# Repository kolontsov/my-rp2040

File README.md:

# My-RP2040

A small [RP2040](https://datasheets.raspberrypi.com/rp2040/rp2040-datasheet.pdf) board, with USB-C, 8MB of flash, SWD interface, 22 GPIO, and a LED. Size: 24x37mm.

This board serves no special purpose other than being an exercise in designing an RP2040 board.

- Designed in KiCad 8, manufactured and assembled at [JLCPCB](https://jlcpcb.com/), confirmed to work.
- Follows recommendation from the [Hardware design with RP2040](https://datasheets.raspberrypi.com/rp2040/hardware-design-with-rp2040.pdf).
- Some footprints and 3D models are from my [personal library](https://github.com/kolontsov/kicad-lib).
- Uses [design rules](https://github.com/labtroll/KiCad-DesignRules) to match JLCPCB [capabilities](https://jlcpcb.com/capabilities/pcb-capabilities).
- Production files (Gerbers, BOM, and CPL) are generated with the help of the [KiCad JLCPCB plugin](https://github.com/Bouni/kicad-jlcpcb-tools).

## Pinout

## License

Creative Commons (CC0-1.0). For the license text, see [LICENSE](LICENSE).

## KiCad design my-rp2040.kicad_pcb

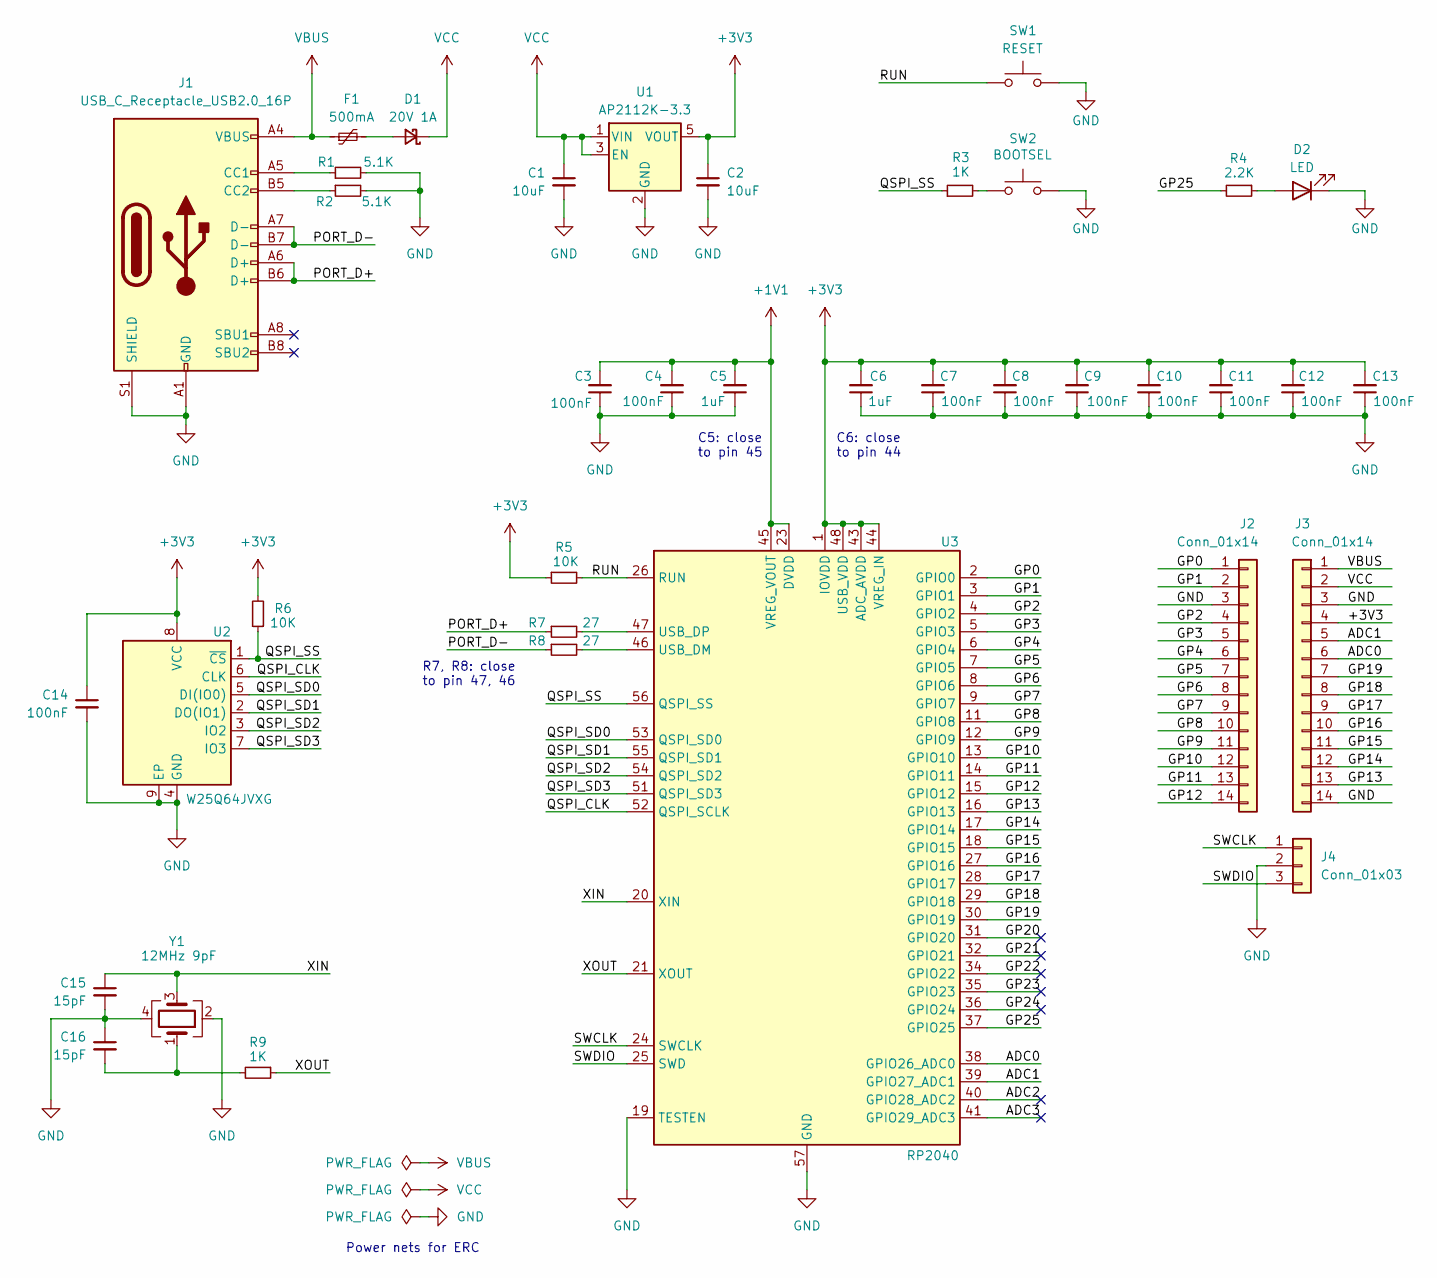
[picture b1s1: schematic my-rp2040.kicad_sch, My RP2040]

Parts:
C1, C2: 10uF; C_0402_1005Metric; MPN CL05A106MQ5NUNC; LCSC C15525
C3, C4, C7, C8, C9, C10, C11, C12, C13, C14: 100nF; C_0402_1005Metric; MPN CL05B104KO5NNNC; LCSC C1525
C5, C6: 1uF; C_0402_1005Metric; MPN CL05A105KA5NQNC; LCSC C52923
C15, C16: 15pF; C_0402_1005Metric; MPN 0402CG150J500NT; LCSC C1548
D1: 20V 1A; D_SOD-323; MPN B5817WS; LCSC C123899
D2: LED; LED_0603_1608Metric; MPN 19-213/Y2C-CQ2R2L/3T(CY); LCSC C72038
F1: 500mA; Fuse_0603_1608Metric; MPN MF-FSMF050X-2; LCSC C210357
J1: USB_C_Receptacle_USB2.0_16P; USB_C_Receptacle_HRO_TYPE-C-31-M-12; MPN TYPE-C-31-M-12; LCSC C165948
J2, J3: Conn_01x14; PinHeader_1x14_P2.54mm_Vertical
J4: Conn_01x03; PinHeader_1x03_P2.54mm_Vertical
R1, R2: 5.1K; R_0402_1005Metric; MPN 0402WGF5101TCE; LCSC C25905
R3, R9: 1K; R_0402_1005Metric; MPN 0402WGF1001TCE; LCSC C11702
R4: 2.2K; R_0402_1005Metric; MPN 0402WGF2201TCE; LCSC C25879
R5, R6: 10K; R_0402_1005Metric; MPN 0402WGF1002TCE; LCSC C25744
R7, R8: 27; R_0402_1005Metric; MPN 0402WGF270JTCE; LCSC C25100
SW1: RESET; SW-SMD-TS-1088-AR02016; MPN TS-1088-AR02016; LCSC C720477
SW2: BOOTSEL; SW-SMD-TS-1088-AR02016; MPN TS-1088-AR02016; LCSC C720477
U1: AP2112K-3.3; SOT-23-5; MPN AP2112K-3.3TRG1; LCSC C51118
U2: W25Q64JVXG; XSON-8_L4.0-W4.0-P0.80-TL-EP; MPN W25Q64JVXGIQ; LCSC C2940195
U3: RP2040; QFN-56-1EP_7x7mm_P0.4mm_EP3.2x3.2mm; MPN RP2040; LCSC C2040
Y1: 12MHz 9pF; Crystal_SMD_2520-4Pin_2.5x2.0mm; MPN 2TJ412000HYGBC; LCSC C2149204

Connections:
+1V1: C3.2, C4.2, C5.2, U3.23 (DVDD), U3.45 (VREG_VOUT), U3.50 (DVDD)
+3V3: C2.1, C6.2, C7.2, C8.2, C9.2, C10.2, C11.2, C12.2, C13.2, C14.1, J3.4, R5.1, R6.2, U1.5 (VOUT), U2.8 (VCC), U3.1 (IOVDD), U3.10 (IOVDD), U3.22 (IOVDD), U3.33 (IOVDD), U3.42 (IOVDD), U3.43 (ADC_AVDD), U3.44 (VREG_IN), U3.48 (USB_VDD), U3.49 (IOVDD)
/ADC0: J3.6, U3.38 (GPIO26_ADC0)
/ADC1: J3.5, U3.39 (GPIO27_ADC1)
/ADC2: U3.40 (GPIO28_ADC2)
/ADC3: U3.41 (GPIO29_ADC3)
/GP0: J2.1, U3.2 (GPIO0)
/GP1: J2.2, U3.3 (GPIO1)
/GP2: J2.4, U3.4 (GPIO2)
/GP3: J2.5, U3.5 (GPIO3)
/GP4: J2.6, U3.6 (GPIO4)
/GP5: J2.7, U3.7 (GPIO5)
/GP6: J2.8, U3.8 (GPIO6)
/GP7: J2.9, U3.9 (GPIO7)
/GP8: J2.10, U3.11 (GPIO8)
/GP9: J2.11, U3.12 (GPIO9)
/GP10: J2.12, U3.13 (GPIO10)
/GP11: J2.13, U3.14 (GPIO11)
/GP12: J2.14, U3.15 (GPIO12)
/GP13: J3.13, U3.16 (GPIO13)
/GP14: J3.12, U3.17 (GPIO14)
/GP15: J3.11, U3.18 (GPIO15)
/GP16: J3.10, U3.27 (GPIO16)
/GP17: J3.9, U3.28 (GPIO17)
/GP18: J3.8, U3.29 (GPIO18)
/GP19: J3.7, U3.30 (GPIO19)
/GP20: U3.31 (GPIO20)
/GP21: U3.32 (GPIO21)
/GP22: U3.34 (GPIO22)
/GP23: U3.35 (GPIO23)
/GP24: U3.36 (GPIO24)
/GP25: R4.2, U3.37 (GPIO25)
/PORT_D+: J1.A6 (D+), J1.B6 (D+), R7.1
/PORT_D-: J1.A7 (D-), J1.B7 (D-), R8.1
/QSPI_CLK: U2.6 (CLK), U3.52 (QSPI_SCLK)
/QSPI_SD0: U2.5 (DI(IO0)), U3.53 (QSPI_SD0)
/QSPI_SD1: U2.2 (DO(IO1)), U3.55 (QSPI_SD1)
/QSPI_SD2: U2.3 (IO2), U3.54 (QSPI_SD2)
/QSPI_SD3: U2.7 (IO3), U3.51 (QSPI_SD3)
/QSPI_SS: R3.1, R6.1, U2.1 (~CS), U3.56 (QSPI_SS)
/RUN: R5.2, SW1.1, U3.26 (RUN)
/SWCLK: J4.1, U3.24 (SWCLK)
/SWDIO: J4.3, U3.25 (SWD)
/XIN: C15.1, U3.20 (XIN), Y1.3
/XOUT: R9.1, U3.21 (XOUT)
GND: C1.2, C2.2, C3.1, C4.1, C5.1, C6.1, C7.1, C8.1, C9.1, C10.1, C11.1, C12.1, C13.1, C14.2, C15.2, C16.1, D2.1 (K), J1.A1 (GND), J1.A12 (GND), J1.B1 (GND), J1.B12 (GND), J1.S1 (SHIELD), J2.3, J3.3, J3.14, J4.2, R1.2, R2.2, SW1.2, SW2.2, U1.2 (GND), U2.4 (GND), U2.9 (EP), U3.19 (TESTEN), U3.57 (GND), Y1.2, Y1.4
unnamed: C16.2, R9.2, Y1.1
unnamed: D1.2 (A), F1.2
unnamed: D2.2 (A), R4.1
unnamed: J1.A5 (CC1), R1.1
unnamed: J1.B5 (CC2), R2.1
unnamed: R3.2, SW2.1
unnamed: R8.2, U3.46 (USB_DM)
unnamed: R7.2, U3.47 (USB_DP)
VBUS: F1.1, J1.A4 (VBUS), J1.A9 (VBUS), J1.B4 (VBUS), J1.B9 (VBUS), J3.1
VCC: C1.1, D1.1 (K), J3.2, U1.1 (VIN), U1.3 (EN)

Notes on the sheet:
R7, R8: close to pin 47, 46
Power nets for ERC
C5: close to pin 45
C6: close to pin 44

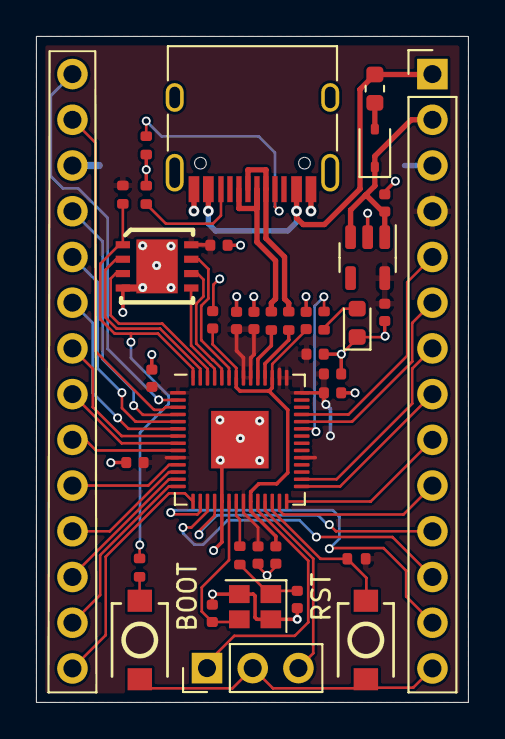
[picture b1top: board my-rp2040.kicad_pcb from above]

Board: 2 copper layers, 24.0 x 37.0 mm, 38 parts (0 on the bottom side), 49 nets.

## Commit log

2024-03-15 add .DS_Store
2024-03-15 add manufactured board image
2024-03-15 add README
